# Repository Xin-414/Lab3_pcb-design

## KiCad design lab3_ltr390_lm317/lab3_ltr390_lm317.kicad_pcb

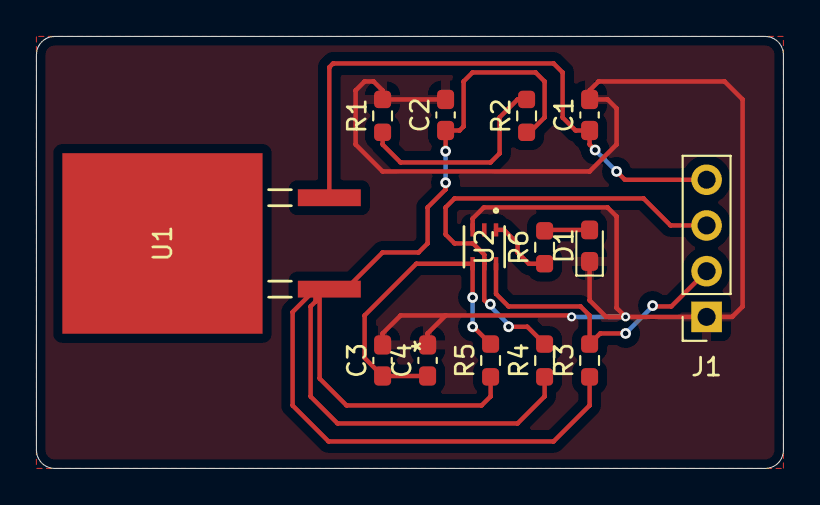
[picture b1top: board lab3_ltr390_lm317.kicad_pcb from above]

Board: 2 copper layers, 41.5 x 24.0 mm, 14 parts (0 on the bottom side), 8 nets.

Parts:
C1, C3: 0.1µF; C_0603_1608Metric_Pad1.08x0.95mm_HandSolder
C2: 1.0µF; C_0603_1608Metric_Pad1.08x0.95mm_HandSolder
C4: 4.7µF; C_0603_1608Metric_Pad1.08x0.95mm_HandSolder
D1: LED; LED_0603_1608Metric_Pad1.05x0.95mm_HandSolder
J1: Conn_01x04_Pin; PinSocket_1x04_P2.54mm_Vertical
R1: 390Ω; R_0603_1608Metric_Pad0.98x0.95mm_HandSolder
R2: 240Ω; R_0603_1608Metric_Pad0.98x0.95mm_HandSolder
R3, R4, R5: 4.7kΩ; R_0603_1608Metric_Pad0.98x0.95mm_HandSolder
R6: 1kΩ; R_0603_1608Metric_Pad0.98x0.95mm_HandSolder
U1: LM317BD2TG; D2PAK3_ONS
U2: LTR-390UV-01; SMD6_LTR-390UV-01_LTO

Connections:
+3.3V: C2.1, R2.1, R3.1, R4.1, R5.1, U1.1 (OUT)
+3V3: C3.1, C4.1, R5.2, R6.1, U2.1 (VDD), U2.4 (INT)
/SCL: J1.3, R4.2, U2.5 (SCL)
/SDA: J1.2 (SDA), R3.2, U2.6 (SDA)
GND: C1.2, C2.2, C3.2, C4.2, D1.1 (K), J1.1, R1.2, U2.3 (GND)
unnamed: D1.2 (A), R6.2
unnamed: R1.1, R2.2
VCC: C1.1, J1.4, U1.3 (VIN)

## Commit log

2026-01-30 Upload KiCAD project files
2026-01-30 Additional footprint and symbol
2026-01-30 Upload BOM
